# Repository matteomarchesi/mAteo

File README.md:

# mAteo

mAteo is a small and simple weather station build on Arduino Nano.

It implements measures of temperature, humidity and pressure using DH22 (tempetaure and umidity) and BMP180 (pressure) sensors modules.
It also implements a clock build with "1 wire" approach (
[inspired from here](http://www.instructables.com/id/Make-an-accurate-Arduino-clock-using-only-one-wire/)).
Data are shown on a 0.96" SSD1306 OLED display.
The user can interact with a 5 keys keyboard, build on the basis of Arduino starter kit tutorial, that use only 1 analog input.

Real time data are shown on screen all together.
Graphs of last 24hrs (1 point each 30') are on separated screens.
Data for graph are stored in EEPROM.

## BOM
- Arduino NANO
- DHT22 temperature and humidity sensor
- BMP180 temparture and pressure sensor
- SSD1306 0.96" OLED display
- 5 pushbuttons
- 1 220ohm resistor
- 1 2kohm resistor
- 1 4.7kohm resistor
- 2 10kohm resistors

## Arduino pin used
Single wire clock
- D2 interrupt
- D3 PWM used for clock

keyboard
- A6

I2C
- A4 SDA
- A5 SCL

Power supply of components
- 5V
- GND

Arduino NANO is powerd with onboard USB.

## SW dependencies
- Wire
- SFE_BMP180
- DHT *
- Adafruid_GFX *
- Adafruid_SSD1306 *
- EEPROM

(*) these have been modified to reduce memory footprint and have not been uploaded yet on my github.

## how to use
chapter to be witten

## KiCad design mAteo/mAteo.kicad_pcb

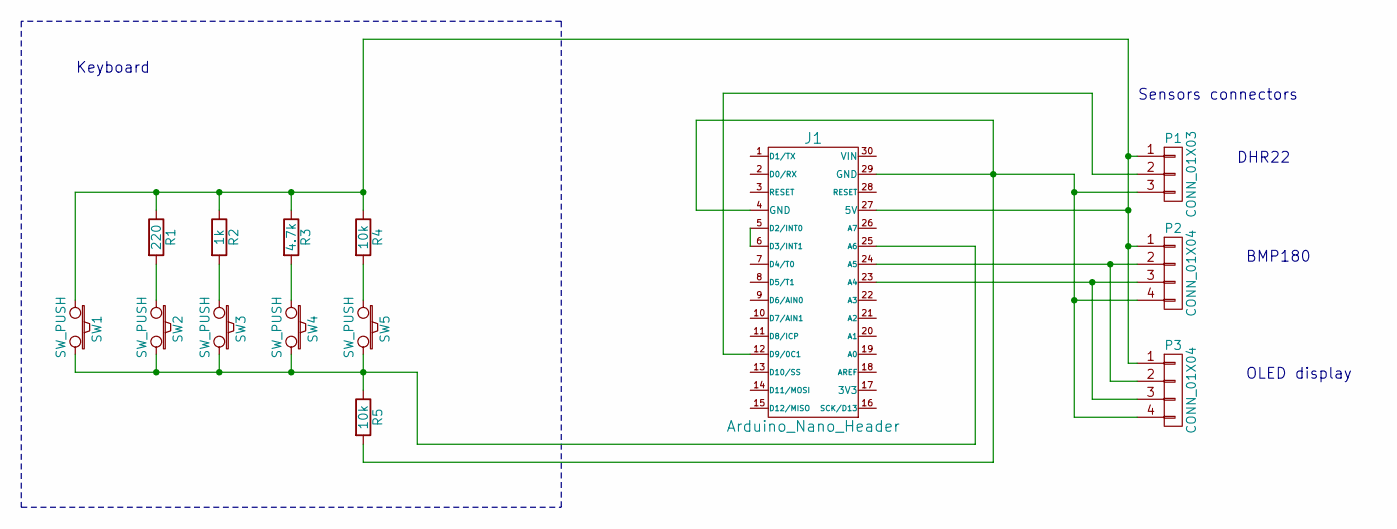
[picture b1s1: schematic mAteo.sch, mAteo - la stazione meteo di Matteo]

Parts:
J1: Arduino_Nano_Header; arduino_nano_header
P1: CONN_01X03; pin_strip_3
P2, P3: CONN_01X04; pin_strip_4
R1: 220; RC03
R2: 1k; RC03
R3: 4.7k; RC03
R4, R5: 10k; RC03
SW1, SW2, SW3, SW4, SW5: SW_PUSH; PCB_PUSH

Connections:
unnamed: J1.5 (D2/INT0), J1.6 (D3/INT1)
unnamed: J1.12 (D9/0C1), P1.2
unnamed: J1.23 (A4), P2.3, P3.3
unnamed: J1.24 (A5), P2.2, P3.2
unnamed: J1.25 (A6), R5.1, SW1.2, SW2.2, SW3.2, SW4.2, SW5.2
unnamed: J1.27 (5V), P1.1, P2.1, P3.1, R1.1, R2.1, R3.1, R4.1, SW1.1
unnamed: J1.4 (GND), J1.29 (GND), P1.3, P2.4, P3.4, R5.2
unnamed: R1.2, SW2.1
unnamed: R2.2, SW3.1
unnamed: R3.2, SW4.1
unnamed: R4.2, SW5.1

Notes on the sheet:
Keyboard
Sensors connectors
DHR22
BMP180
OLED display

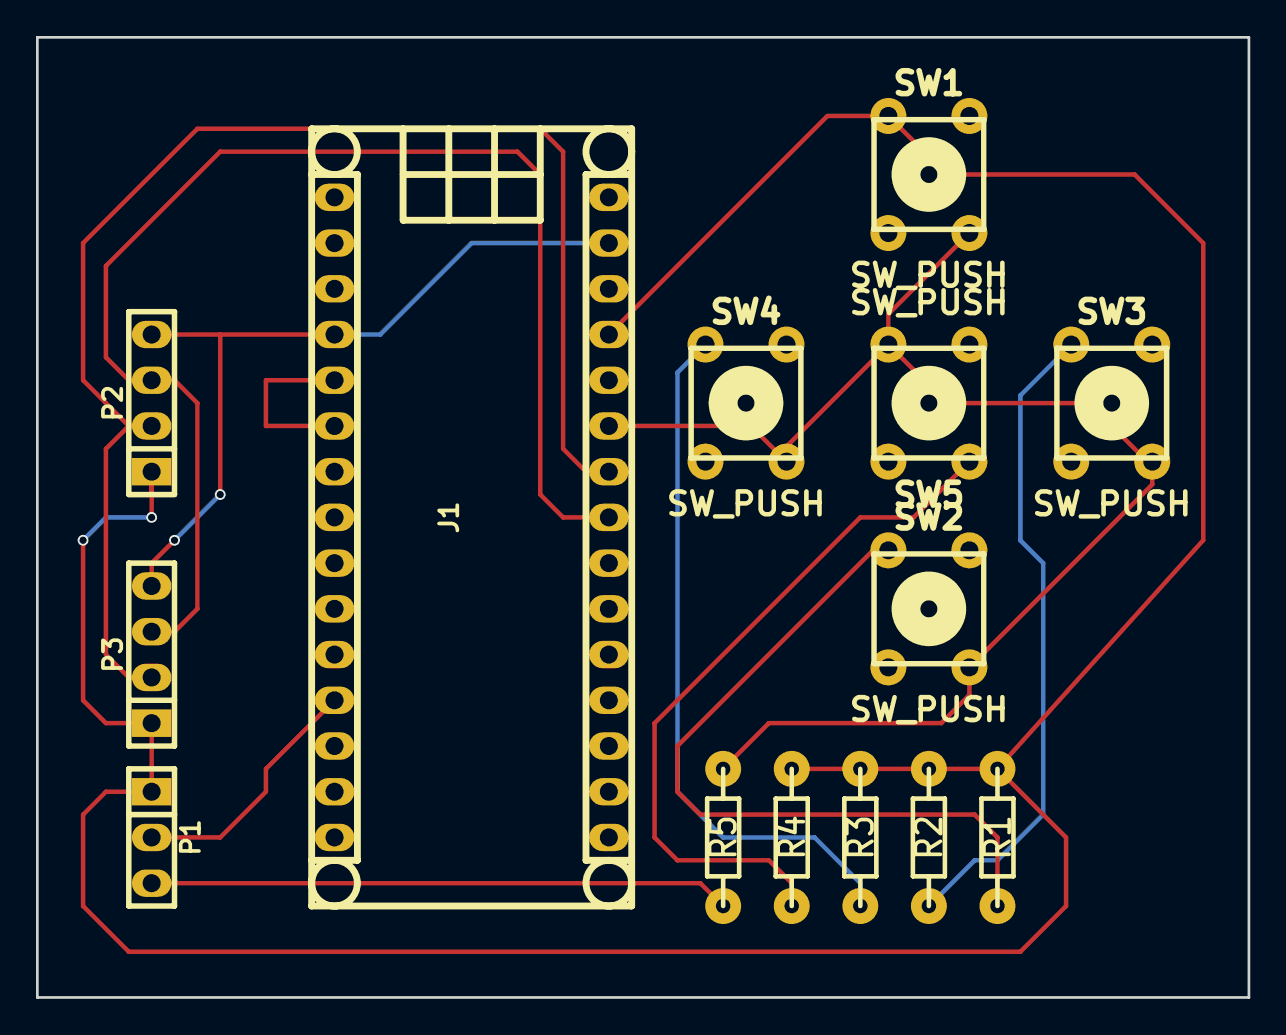
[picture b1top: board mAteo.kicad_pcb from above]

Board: 2 copper layers, 67.3 x 53.3 mm, 14 parts (0 on the bottom side), 11 nets.

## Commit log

2016-12-04 startind development
2016-12-04 README and LICENSE
2016-12-04 license filled
2016-12-05 with date
2016-12-05 abbozzo tastiera
2016-12-30 date and time set by compiling date/time; 3 screens of function (off, std, funct 2); antibounce.
2017-01-09 new display layout. set time and date
2017-01-10 set_clock: bar over element that can be updated. s_c renamed in set_clock.
2017-01-10 ADDED: battery voltage measure function(within readSensors function). FIDED: compiling month assignment.
2017-01-11 FIXED: readsensor --> battery voltage measures now consider the voltage partition ADDED: float2int function --> to round float to nearest int ADDED: batteryICO --> to draw battery icon instead of wri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
2017-01-13 workingnotes.txt added
2017-01-14 mAteo.fzz
    ADDED: mAteo.fzz schematics (include only Arduino nano and keyboard circuitry)
    mAteo.ini
    MODIF: keyboard value.
    removed battery measurement
2017-01-14 mAteo.fzz
    ADDED: "clock" wire
2017-01-15 MODIF: mAteo.fzz completed the schematic and the breadboard
2017-01-16 ADDED: graph for temperature
2017-01-22 ADDED: 3 graphs MODIF: Adafruit libraries cut to reduce memory fotprint (not so useful by the way)
2017-01-23 mAteo.fzz MODIF: DHT pin is now D9
    mAteo.ino
    MODIF: DHT pin is now D9
    FIXED: graph now seems to work correctly
2017-01-24 mAteo.ino
    MODIF: array with values for graphs are now stored in EEPROM
2017-01-25 mAteo.ino FIXED: modified approach with EEPROM to reduce writing. Now it use a pointer to address which location to read. The EEPROM "array" is a "circle", i.e. after position 47 there is 0.
    mempointer points to next data to be written
    writes data in position 0, 1, 2 ...
    store position 0 1 2 3 4 5 6 7
    mempointer x-1 x P older data
    for graph |--------------->
    ------->P
2017-01-26 mAteo.ino FIXED: ** readSensor correct rollover of mempointer
    ** graphE
    added mempointer within passed parameters
    added few local variables (gdata, gi)
    indexes are now uint_8 (i, gi, pnt, pntp)
    introduced new gi index to correctly manage graphs printout
2017-01-27 code cleanup
2017-01-30 FIXED: clockCounter() several errors in if () written as (dd = 29) instead of (dd == 29) set_clock() added checks to avoid negative numbers and to exceed the max possibble value
2017-01-30 removed unnecessary files
2017-01-30 bug fixed in main branch
2017-01-30 more bug fixed in main branch
2017-02-01 README.md rewritten
2017-02-01 few control variable changed from int to uint8_t
    printTime is now String printTime2() + String twodigits(int val) to simplify the code
2017-02-01 BUGFIX: mAteo.ino varialbles used for time management changed from uint8_t to int8_t, to correctly manage the set_time
2017-02-02 BUGFIX: readSensor() now it should actually store a value each 30 min. I hope...
2017-02-02 commented Serial.print
2017-02-03 ADDED: management of 1st startup or corrupted memory
2017-02-03 ADDED schematics in mAteo folder
2017-02-07 fixed comments from git
2017-02-15 keyboard reshuffled
